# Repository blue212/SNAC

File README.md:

# SNAC
Accessory converter for MiSTer

Serial Native Accessory Converter

SNAC is general purpose level shifter for use with MiSTer. It can be used to power 5v devices and it will safely convert any logic between the 3v3(MiSTer) and 5 device. It will be used mostly for 5v controllers and other peripherals.

The SNAC connects to the User port(formerly Serial I/O port) of the IO board on Mister. I recommend a male to female usb3 extension cable between them.

The SNAC is available in 2 versions the only difference being the connector on the controller side(USB3 or HDMI). Various adapters can then be plugged into that connector. I made various adapter PCBs for use with the USB3 verrsion.

Becasue the SNAC connects to the User port the peripheral connects to the GPIO of the MiSTer, this bypasses all layers the normal usb controllers use. So it's very much like having a controller port for the original system. One benefit of this is that most weird peripherals should work with their cores(like Lightguns etc) which most normal usb converters either don't or can't do. One downside to bypassing the layers is the you can't controle the OSD.

*A mod to the older IO boards is needed if you want to use SEGA peripherals. Analog IO board 6.1 and Digital 1.2 fix this issue and have a jumper near USER port that needs to be set to io6 .

-TODO detail the needed mod

-Updates

Changed the partslist to use a different part for the male USB connector.

Uxcell a19032000ux0260 instead of Wuerth 692112030100

Addded Mini version of the hdmi and USB3 snac boards.

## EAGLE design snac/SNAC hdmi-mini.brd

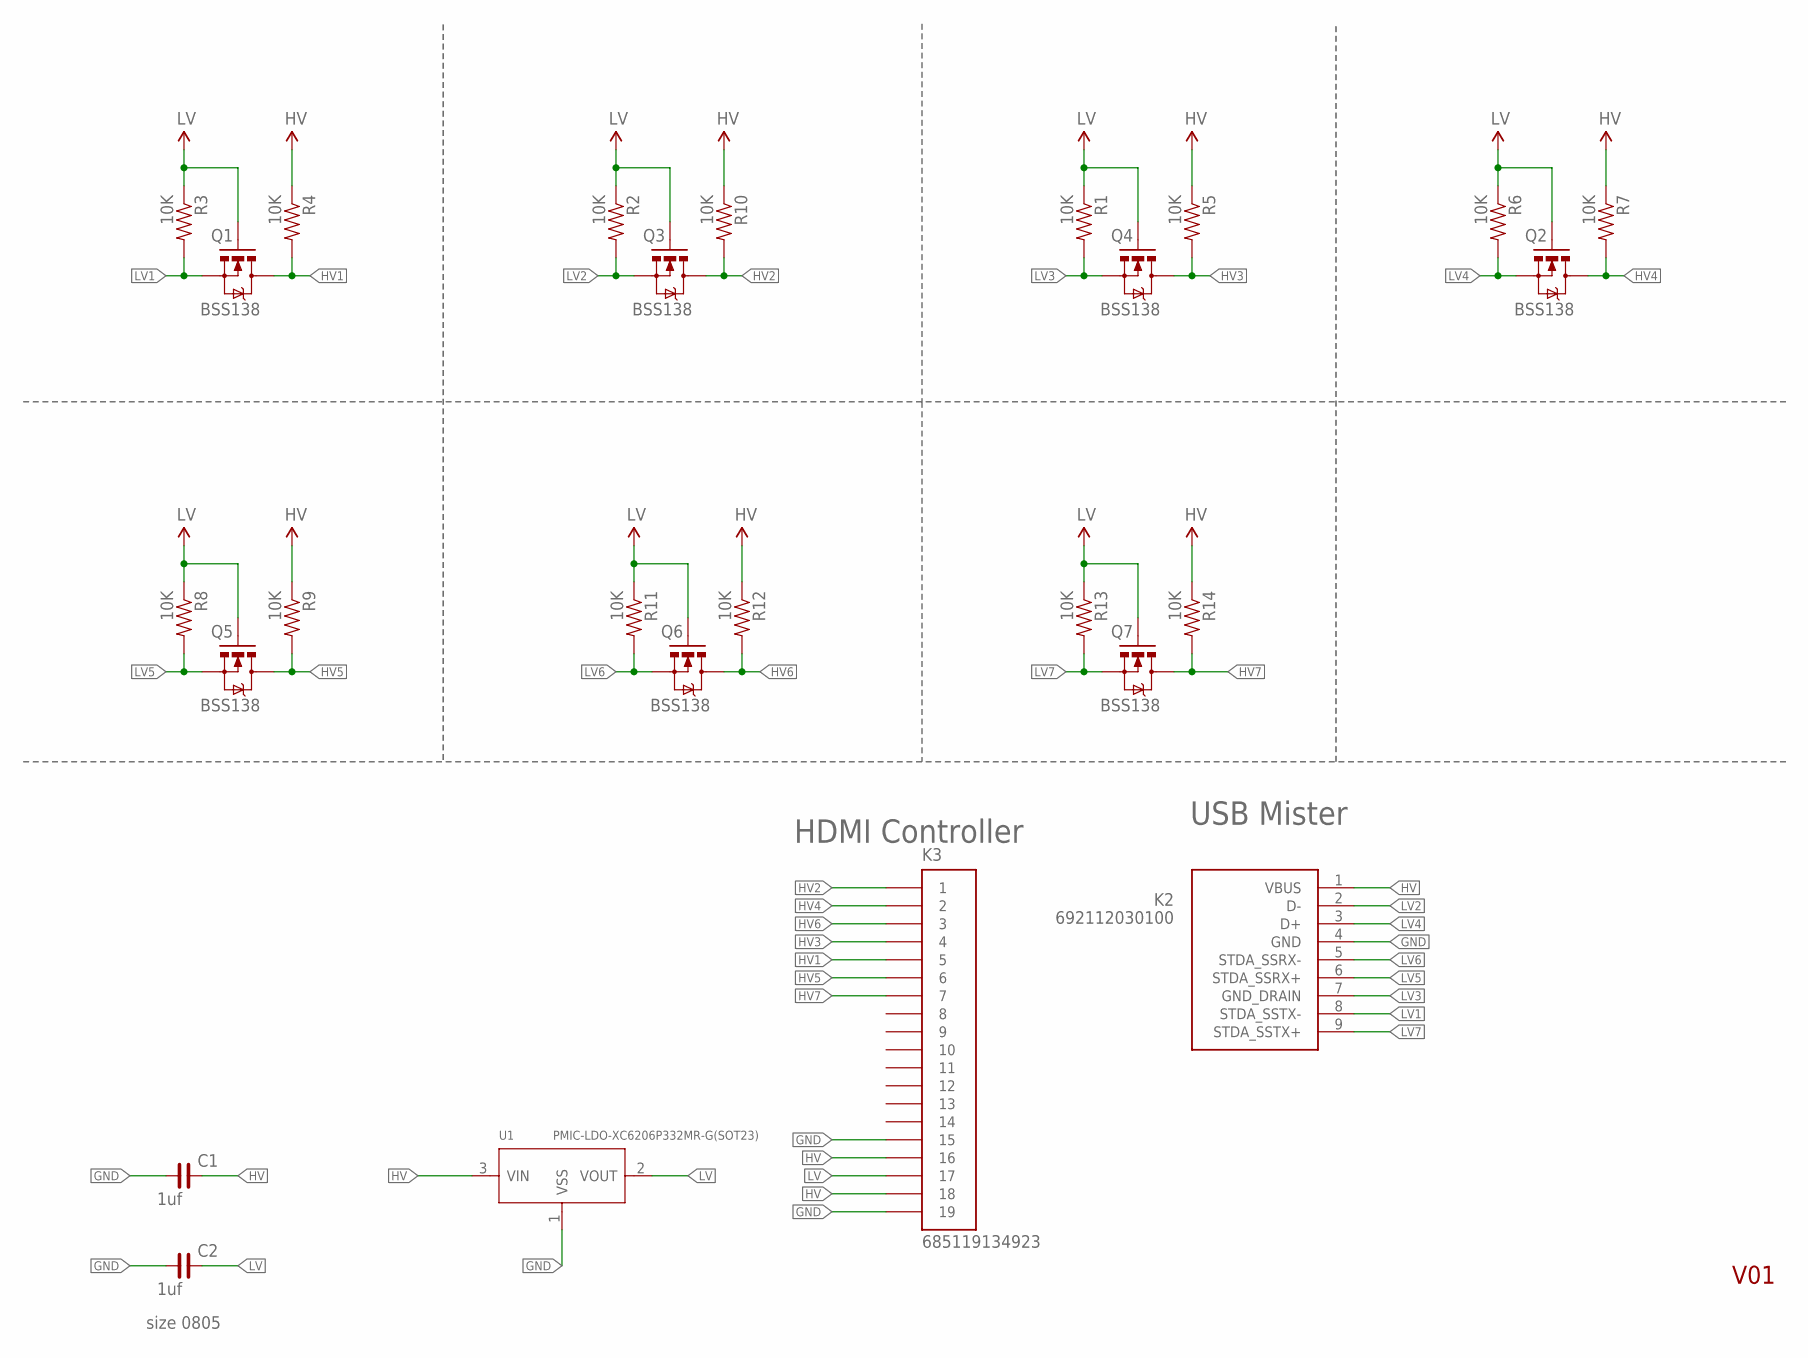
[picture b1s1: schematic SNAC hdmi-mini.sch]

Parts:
C1, C2: 1uf; C0805
K2: 692112030100
K3: 685119134923
Q1, Q2, Q3, Q4, Q5, Q6, Q7: BSS138; SOT23-3
R1, R2, R3, R4, R5, R6, R7, R8, R9, R10, R11, R12, R13, R14: 10K; 0603-RES
U1: PMIC-LDO-XC6206P332MR-G(SOT23); SOT-23

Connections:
GND: C1.1, C2.1, K2.4 (GND), K3.15, K3.19, U1.1 (VSS)
HV: C1.2, K2.1 (VBUS), K3.16, K3.18, R4.1, R5.1, R7.1, R9.1, R10.1, R12.1, R14.1, U1.3 (VIN)
HV1: K3.5, Q1.3 (D), R4.2
HV2: K3.1, Q3.3 (D), R10.2
HV3: K3.4, Q4.3 (D), R5.2
HV4: K3.2, Q2.3 (D), R7.2
HV5: K3.6, Q5.3 (D), R9.2
HV6: K3.3, Q6.3 (D), R12.2
HV7: K3.7, Q7.3 (D), R14.2
LV: C2.2, K3.17, Q1.1 (G), Q2.1 (G), Q3.1 (G), Q4.1 (G), Q5.1 (G), Q6.1 (G), Q7.1 (G), R1.1, R2.1, R3.1, R6.1, R8.1, R11.1, R13.1, U1.2 (VOUT)
LV1: K2.8 (STDA_SSTX-), Q1.2 (S), R3.2
LV2: K2.2 (D-), Q3.2 (S), R2.2
LV3: K2.7 (GND_DRAIN), Q4.2 (S), R1.2
LV4: K2.3 (D+), Q2.2 (S), R6.2
LV5: K2.6 (STDA_SSRX+), Q5.2 (S), R8.2
LV6: K2.5 (STDA_SSRX-), Q6.2 (S), R11.2
LV7: K2.9 (STDA_SSTX+), Q7.2 (S), R13.2

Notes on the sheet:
V01
USB Mister
size 0805
HDMI Controller

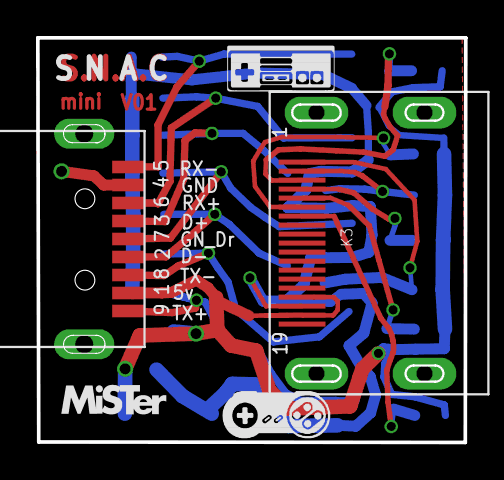
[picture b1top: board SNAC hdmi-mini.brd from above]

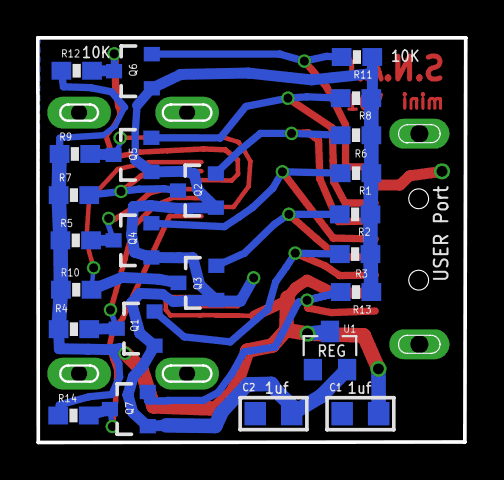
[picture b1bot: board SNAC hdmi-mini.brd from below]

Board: 2 copper layers, 23.8 x 22.5 mm, 26 parts (24 on the bottom side), 17 nets.

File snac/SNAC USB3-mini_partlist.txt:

Partlist

EAGLE Version 7.7.0 Copyright (c) 1988-2016 CadSoft

Assembly variant: 

Part     Value                          Package         Library                          Position (inch)       Orientation

C1       1uf                            C0805           rc-master-smd                   (0.23239998 0.06189998) MR0
C2       1uf                            C0805           rc-master-smd                   (0.42249975 0.062)    MR0
K1       692121030100                   692121030100    Wuerth_Elektronik               (1.86 0.42)           R270
K2       a19032000ux0260                a19032000ux0260 Uxcell                          (0.2 0.42)            R90
Q1       BSS138                         SOT23-3         SparkFun                        (0.734 0.194)         MR90
Q2       BSS138                         SOT23-3         SparkFun                        (0.729 0.565)         MR90
Q3       BSS138                         SOT23-3         SparkFun                        (0.73 0.317)          MR90
Q4       BSS138                         SOT23-3         SparkFun                        (0.729 0.441)         MR90
Q5       BSS138                         SOT23-3         SparkFun                        (0.729 0.689)         MR90
Q6       BSS138                         SOT23-3         SparkFun                        (0.728 0.811)         MR90
Q7       BSS138                         SOT23-3         SparkFun                        (0.731 0.072)         MR90
R1       10K                            0603-RES        SparkFun                        (0.242 0.588)         MR180
R2       10K                            0603-RES        SparkFun                        (0.244 0.498)         MR180
R3       10K                            0603-RES        SparkFun                        (0.244 0.411)         MR180
R4       10K                            0603-RES        SparkFun                        (0.86210002 0.19380007) MR0
R5       10K                            0603-RES        SparkFun                        (0.855 0.441)         MR0
R6       10K                            0603-RES        SparkFun                        (0.242 0.671)         MR180
R7       10K                            0603-RES        SparkFun                        (0.856 0.565)         MR0
R8       10K                            0603-RES        SparkFun                        (0.242 0.752)         MR180
R9       10K                            0603-RES        SparkFun                        (0.853 0.689)         MR0
R10      10K                            0603-RES        SparkFun                        (0.859 0.317)         MR0
R11      10K                            0603-RES        SparkFun                        (0.24 0.842)          MR180
R12      10K                            0603-RES        SparkFun                        (0.853 0.812)         MR0
R13      10K                            0603-RES        SparkFun                        (0.242 0.328)         MR180
R14      10K                            0603-RES        SparkFun                        (0.861 0.071)         MR0
U1       PMIC-LDO-XC6206P332MR-G(SOT23) SOT-23          PMIC-LDO-XC6206P332MR-G_SOT23_  (0.299 0.2)           MR0

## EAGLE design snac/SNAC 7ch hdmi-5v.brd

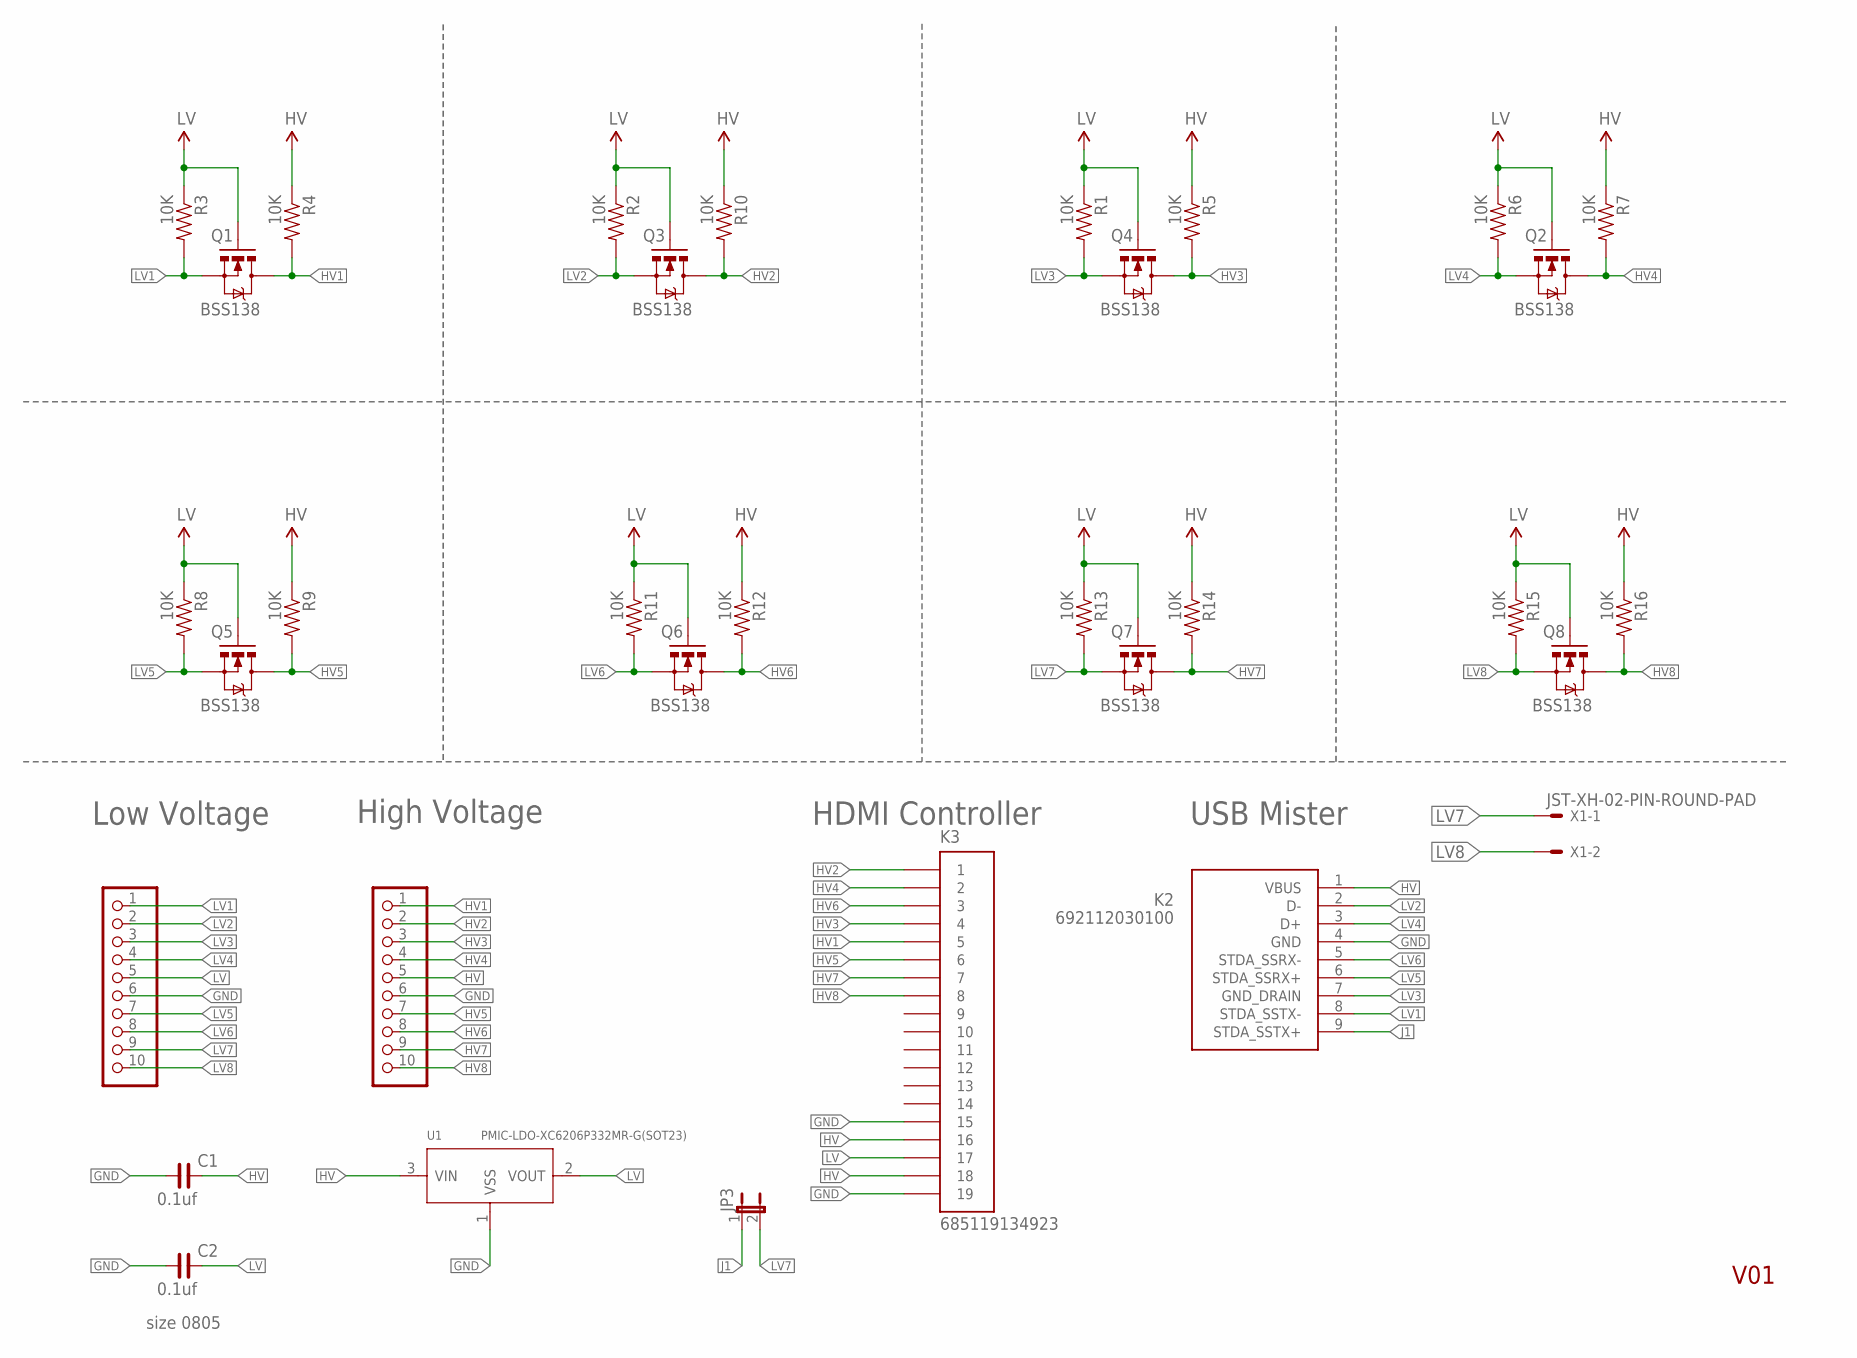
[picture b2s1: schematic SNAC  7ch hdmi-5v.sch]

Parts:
C1, C2: 0.1uf; C0805
JP1, JP2: PINHD-1X10_2.54-S; 1X10-S
JP3: JUMPER-2PTH; 1X02
K2: 692112030100
K3: 685119134923
Q1, Q2, Q3, Q4, Q5, Q6, Q7, Q8: BSS138; SOT23-3
R1, R2, R3, R4, R5, R6, R7, R8, R9, R10, R11, R12, R13, R14, R15, R16: 10K; 0603-RES
U1: PMIC-LDO-XC6206P332MR-G(SOT23); SOT-23
X1: JST-XH-02-PIN-ROUND-PAD; JST-XH-02-PACKAGE-ROUND-PAD

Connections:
GND: C1.1, C2.1, JP1.6, JP2.6, K2.4 (GND), K3.15, K3.19, U1.1 (VSS)
HV: C1.2, JP2.5, K2.1 (VBUS), K3.16, K3.18, R4.1, R5.1, R7.1, R9.1, R10.1, R12.1, R14.1, R16.1, U1.3 (VIN)
HV1: JP2.1, K3.5, Q1.3 (D), R4.2
HV2: JP2.2, K3.1, Q3.3 (D), R10.2
HV3: JP2.3, K3.4, Q4.3 (D), R5.2
HV4: JP2.4, K3.2, Q2.3 (D), R7.2
HV5: JP2.7, K3.6, Q5.3 (D), R9.2
HV6: JP2.8, K3.3, Q6.3 (D), R12.2
HV7: JP2.9, K3.7, Q7.3 (D), R14.2
HV8: JP2.10, K3.8, Q8.3 (D), R16.2
J1: JP3.1, K2.9 (STDA_SSTX+)
LV: C2.2, JP1.5, K3.17, Q1.1 (G), Q2.1 (G), Q3.1 (G), Q4.1 (G), Q5.1 (G), Q6.1 (G), Q7.1 (G), Q8.1 (G), R1.1, R2.1, R3.1, R6.1, R8.1, R11.1, R13.1, R15.1, U1.2 (VOUT)
LV1: JP1.1, K2.8 (STDA_SSTX-), Q1.2 (S), R3.2
LV2: JP1.2, K2.2 (D-), Q3.2 (S), R2.2
LV3: JP1.3, K2.7 (GND_DRAIN), Q4.2 (S), R1.2
LV4: JP1.4, K2.3 (D+), Q2.2 (S), R6.2
LV5: JP1.7, K2.6 (STDA_SSRX+), Q5.2 (S), R8.2
LV6: JP1.8, K2.5 (STDA_SSRX-), Q6.2 (S), R11.2
LV7: JP1.9, JP3.2, Q7.2 (S), R13.2, X1.1
LV8: JP1.10, Q8.2 (S), R15.2, X1.2

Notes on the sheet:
High Voltage
Low Voltage
V01
HDMI Controller
USB Mister
size 0805

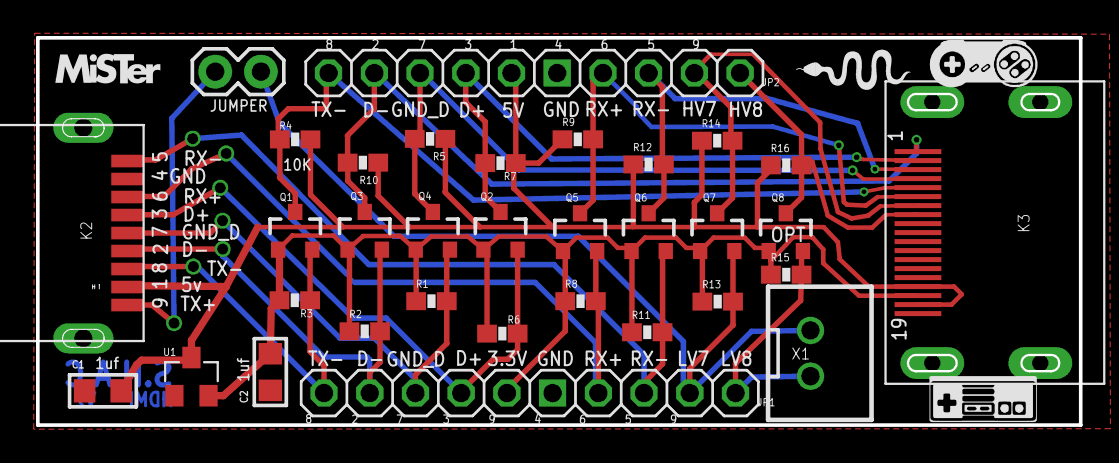
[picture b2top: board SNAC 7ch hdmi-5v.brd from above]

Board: 2 copper layers, 57.9 x 21.5 mm, 33 parts (0 on the bottom side), 20 nets.

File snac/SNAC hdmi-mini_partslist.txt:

Partlist

EAGLE Version 7.7.0 Copyright (c) 1988-2016 CadSoft

Assembly variant: 

Part     Value                          Package         Library                          Position (inch)       Orientation

C1       1uf                            C0805           rc-master-smd                    (0.23239998 0.06189998) MR0
C2       1uf                            C0805           rc-master-smd                    (0.42249975 0.062)    MR0
K2       a19032000ux0260                a19032000ux0260 Uxcell 1                         (0.2 0.444)           R90
K3       685119134923                   685119134923    Wuerth_Elektronik                (0.58 0.435)          R90 
Q1       BSS138                         SOT23-3         SparkFun                         (0.722 0.248)         MR90
Q2       BSS138                         SOT23-3         SparkFun                         (0.588 0.55)          MR90
Q3       BSS138                         SOT23-3         SparkFun                         (0.587 0.348)         MR90
Q4       BSS138                         SOT23-3         SparkFun                         (0.729 0.441)         MR90
Q5       BSS138                         SOT23-3         SparkFun                         (0.729 0.628)         MR90
Q6       BSS138                         SOT23-3         SparkFun                         (0.728 0.811)         MR90
Q7       BSS138                         SOT23-3         SparkFun                         (0.737 0.072)         MR90
R1       10K                            0603-RES        SparkFun                         (0.242 0.588)         MR180
R2       10K                            0603-RES        SparkFun                         (0.244 0.498)         MR180
R3       10K                            0603-RES        SparkFun                         (0.244 0.411)         MR180
R4       10K                            0603-RES        SparkFun                         (0.85910002 0.24680007) MR0
R5       10K                            0603-RES        SparkFun                         (0.855 0.441)         MR0
R6       10K                            0603-RES        SparkFun                         (0.242 0.671)         MR180
R7       10K                            0603-RES        SparkFun                         (0.859 0.54)          MR0
R8       10K                            0603-RES        SparkFun                         (0.242 0.752)         MR180
R9       10K                            0603-RES        SparkFun                         (0.857 0.63)          MR0
R10      10K                            0603-RES        SparkFun                         (0.854 0.333)         MR0
R11      10K                            0603-RES        SparkFun                         (0.24 0.842)          MR180
R12      10K                            0603-RES        SparkFun                         (0.853 0.812)         MR0
R13      10K                            0603-RES        SparkFun                         (0.242 0.328)         MR180
R14      10K                            0603-RES        SparkFun                         (0.86 0.058)          MR0
U1       PMIC-LDO-XC6206P332MR-G(SOT23) SOT-23          PMIC-LDO-XC6206P332MR-G_SOT23_   (0.299 0.2)           MR0

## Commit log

2022-08-16 Added mini versions

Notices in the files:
parts and their libraries:
Wuerth_Elektronik_eiCan_Communication_Co: Copyright: Würth Elektronik
rc-master-smd: Copyright (C) 2007, Bob Starr
